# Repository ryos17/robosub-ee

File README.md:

# Stanford RoboSub — Electrical Repo

Electrical subsystem for the Stanford RoboSub AUV. It includes PCB designs (KiCad), firmware, Python tools, and research.

🌐 [stanfordrobosub.org](https://www.stanfordrobosub.org/)

## Repository layout

- **`platformio.ini`** — PlatformIO config for building/flashing the Teensy firmware. `src_dir` points at one sketch folder; change it to pick which firmware gets flashed (see comments in the file).
- **`gen1/`** — First hardware generation: PCBs only. Deprecated; the sub no longer exists.
- **`gen2/`** — Second (current) generation: PCBs and firmware for the audio and Teensy boards.
- **`gen3/`** — Third generation (in progress): ongoing designs of PCBs with Micro Breakout, Battery Boards, Power Distribution.
- **`imported_parts/`** — Shared KiCad libraries: symbols, footprints, 3D models, import script, and the JLC parts order log.
- **`misc/`** — Older and experimental material.
- **`research/`** — Research work (whisper-based intervehicle communication).

## Sub setup (Jetson Orin)

### Fix the system clock

The Jetson has no battery-backed RTC, so after being powered off its clock can be wrong. A wrong date breaks TLS, so Claude Code, `git`, `pip`, etc. fail to connect. Fix it by syncing over the internet:

```bash
timedatectl                      # check: "System clock synchronized" and the date
sudo timedatectl set-ntp true    # sync the time over the internet
sudo systemctl restart systemd-timesyncd
timedatectl                      # the date should now be correct
```

### Connect to eduroam (Stanford)

Replace `SUNETID` and the password with your own (Stanford eduroam uses PEAP / MSCHAPv2 with `sunetid@stanford.edu` as the identity):

```bash
nmcli connection add type wifi ifname wlP1p1s0 con-name eduroam ssid eduroam \
  wifi-sec.key-mgmt wpa-eap 802-1x.eap peap 802-1x.phase2-auth mschapv2 \
  802-1x.identity SUNETID@stanford.edu 802-1x.password 'YOUR_PASSWORD'
nmcli connection up eduroam
```

If an `eduroam` connection already exists, update it instead of adding a new one:

```bash
nmcli connection modify eduroam 802-1x.identity SUNETID@stanford.edu 802-1x.password 'YOUR_PASSWORD'
nmcli connection up eduroam
```

Don't commit your password. Afterwards, run the clock fix above if Claude still can't connect.

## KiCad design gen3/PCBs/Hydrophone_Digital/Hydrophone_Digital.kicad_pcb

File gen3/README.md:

# Gen 3 Submarine (in progress)

The third hardware generation, currently being designed. The proposed system
architecture is shown below; the boards under [`PCBs/`](PCBs/) are the work
toward it. The current working vehicle is still [`gen2/`](../gen2/).

## PCBs

- **`Micro_Breakout/`** — the main breakout board for gen 3, the successor to
  the gen 2 MLU breakout. References the shared parts library in
  [`../../imported_parts`](../../imported_parts).
- **`Battery_Boards/`** — the gen 3 power-management / battery boards, the
  follow-on to the gen 2 `Power_Management` boards (which had heat problems).
  Two design variants:
  - **`Power_ManagementV3_diode/`** — the diode-based design; this is the lead
    design.
  - **`Power_ManagementV3_eli/`** — Eli's alternative design, kept as a backup.
- **`Power_Distribution/`** — the gen 3 power-distribution board (battery →
  rails).
- **`to_order/`** — staging area for boards that are ready to be fabricated
  (currently empty).

## TODO

- Finalize how signals/power route in and out of `Micro_Breakout`, and choose
  the physical dimensions of all the boards.
- Order the PCBs.

_Last updated: 2026-07-20_

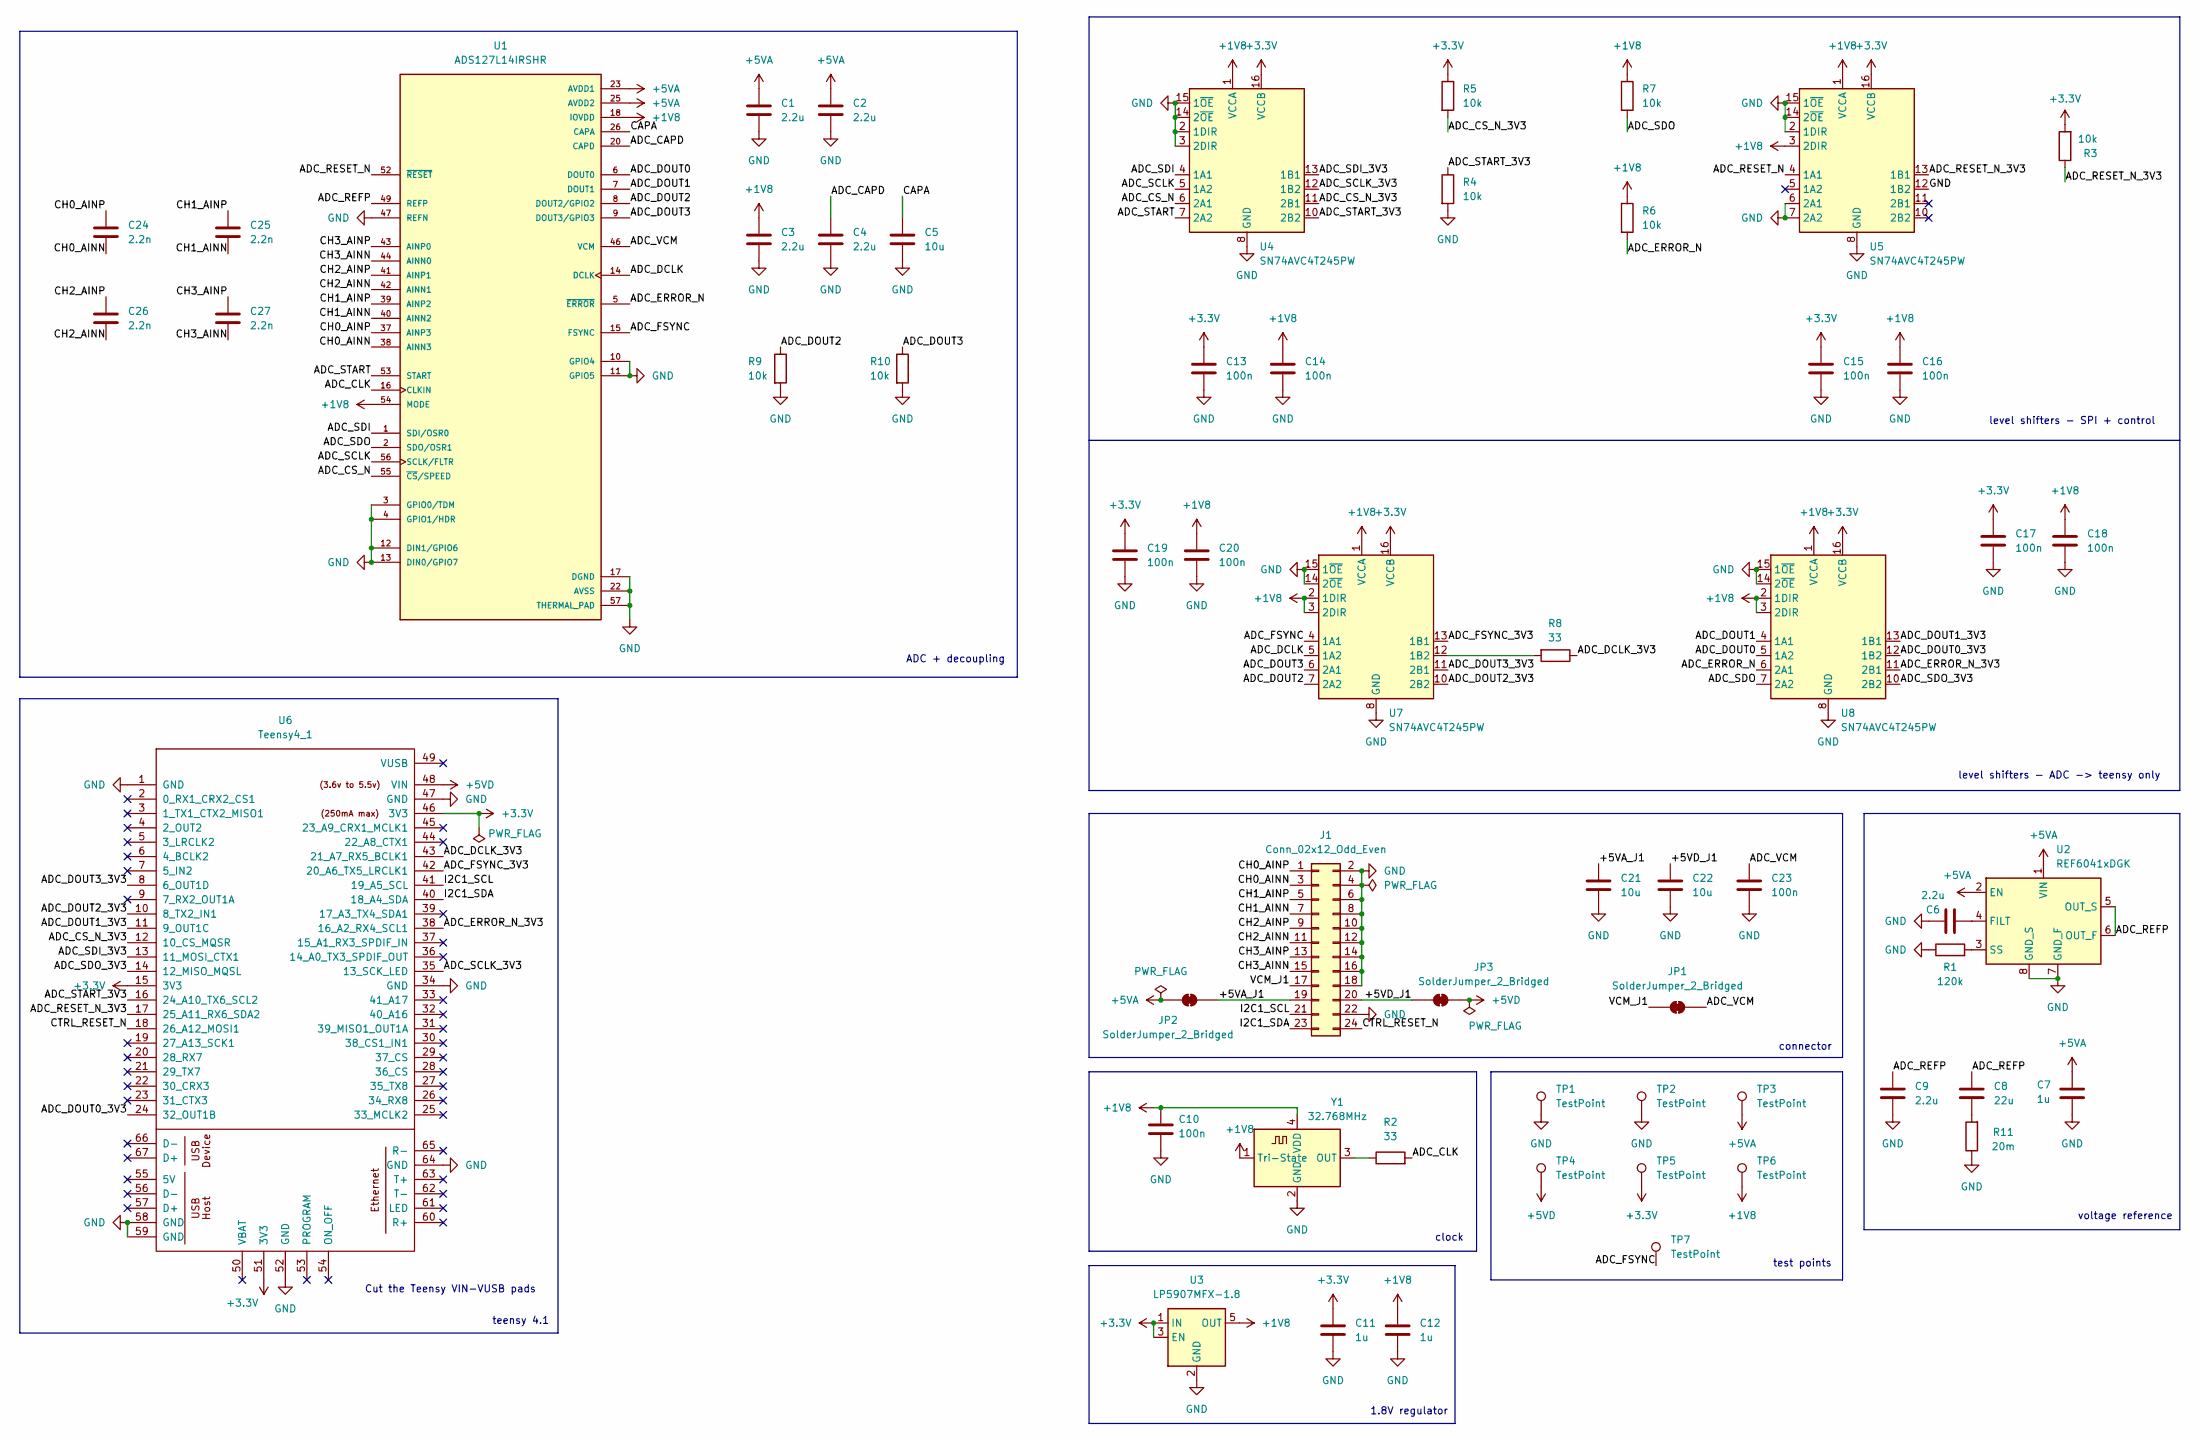
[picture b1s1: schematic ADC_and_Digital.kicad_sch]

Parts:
C1, C2, C3, C4, C6, C9: 2.2u; C_0805_2012Metric_Pad1.18x1.45mm_HandSolder; LCSC C19110
C5, C21, C22: 10u; C_1206_3216Metric_Pad1.33x1.80mm_HandSolder; LCSC C13585
C7, C11, C12: 1u; C_0805_2012Metric_Pad1.18x1.45mm_HandSolder; LCSC C28323
C8: 22u; C_1206_3216Metric_Pad1.33x1.80mm_HandSolder; LCSC C12891
C10, C13, C14, C15, C16, C17, C18, C19, C20, C23: 100n; C_0805_2012Metric_Pad1.18x1.45mm_HandSolder; LCSC C49678
C24, C25, C26, C27: 2.2n; C_0805_2012Metric_Pad1.18x1.45mm_HandSolder; LCSC C28260
J1: Conn_02x12_Odd_Even; PinSocket_2x12_P2.54mm_Horizontal; LCSC C22373936
JP1, JP2, JP3: SolderJumper_2_Bridged; SolderJumper-2_P1.3mm_Bridged_RoundedPad1.0x1.5mm
R1: 120k; R_0805_2012Metric_Pad1.20x1.40mm_HandSolder; LCSC C17436
R2, R8: 33; R_0805_2012Metric_Pad1.20x1.40mm_HandSolder; LCSC C17634
R3, R4, R5, R6, R7, R9, R10: 10k; R_0805_2012Metric_Pad1.20x1.40mm_HandSolder; LCSC C17414
R11: 20m; R_0805_2012Metric_Pad1.20x1.40mm_HandSolder; LCSC C163095
TP1, TP2, TP3, TP4: TestPoint; TestPoint_THTPad_D2.0mm_Drill1.0mm
TP5, TP6: TestPoint; TestPoint_Pad_D1.5mm
TP7: TestPoint; TestPoint_Pad_D1.0mm
U1: ADS127L14IRSHR; IC_ADS127L14IRSHR; PARTREV B; LCSC C46377303
U2: REF6041xDGK; VSSOP-8_3x3mm_P0.65mm; LCSC C2157051
U3: LP5907MFX-1.8; SOT-23-5; LCSC C92498
U4, U5, U7, U8: SN74AVC4T245PW; TSSOP-16_4.4x5mm_P0.65mm; LCSC C81461
U6: Teensy4_1
Y1: 32.768MHz; Oscillator_SMD_ECS_2520MV-xxx-xx-4Pin_2.5x2.0mm; LCSC C5452669

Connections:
+1V8: C3.2, C10.1, C12.1, C14.1, C16.1, C18.1, C20.1, R6.1, R7.1, TP6.1 (1_1), U1.18 (IOVDD), U1.19 (IOVDD), U1.54 (MODE), U3.5 (OUT), U4.1 (VCCA), U5.1 (VCCA), U5.3 (2DIR), U7.1 (VCCA), U7.2 (1DIR), U7.3 (2DIR), U8.1 (VCCA), U8.2 (1DIR), U8.3 (2DIR), Y1.1 (Tri-State), Y1.4 (VDD)
+3.3V: C11.1, C13.1, C15.1, C17.1, C19.1, R3.2, R5.1, TP5.1 (1_1), U3.1 (IN), U3.3 (EN), U4.16 (VCCB), U5.16 (VCCB), U6.15 (3V3), U6.46 (3V3), U6.51 (3V3), U7.16 (VCCB), U8.16 (VCCB)
+5VA: C1.2, C2.2, C7.1, JP2.1 (A), TP3.1 (1_1), U1.23 (AVDD1), U1.24 (AVDD1), U1.25 (AVDD2), U2.1 (VIN), U2.2 (EN)
+5VD: JP3.2 (B), TP4.1 (1_1), U6.48 (VIN)
/ADC_and_Digital/+5VA_J1: C21.1, J1.19, JP2.2 (B)
/ADC_and_Digital/+5VD_J1: C22.1, J1.20, JP3.1 (A)
/ADC_and_Digital/ADC_CAPD: C4.2, U1.20 (CAPD)
/ADC_and_Digital/ADC_CLK: R2.2, U1.16 (CLKIN)
/ADC_and_Digital/ADC_CS_N: U1.55 (~CS/SPEED), U4.6 (2A1)
/ADC_and_Digital/ADC_CS_N_3V3: R5.2, U4.11 (2B1), U6.12 (10_CS_MQSR)
/ADC_and_Digital/ADC_DCLK: U1.14 (DCLK), U7.5 (1A2)
/ADC_and_Digital/ADC_DCLK_3V3: R8.1, U6.43 (21_A7_RX5_BCLK1)
/ADC_and_Digital/ADC_DOUT0: U1.6 (DOUT0), U8.5 (1A2)
/ADC_and_Digital/ADC_DOUT0_3V3: U6.24 (32_OUT1B), U8.12 (1B2)
/ADC_and_Digital/ADC_DOUT1: U1.7 (DOUT1), U8.4 (1A1)
/ADC_and_Digital/ADC_DOUT1_3V3: U6.11 (9_OUT1C), U8.13 (1B1)
/ADC_and_Digital/ADC_DOUT2: R9.1, U1.8 (DOUT2/GPIO2), U7.7 (2A2)
/ADC_and_Digital/ADC_DOUT2_3V3: U6.10 (8_TX2_IN1), U7.10 (2B2)
/ADC_and_Digital/ADC_DOUT3: R10.1, U1.9 (DOUT3/GPIO3), U7.6 (2A1)
/ADC_and_Digital/ADC_DOUT3_3V3: U6.8 (6_OUT1D), U7.11 (2B1)
/ADC_and_Digital/ADC_ERROR_N: R6.2, U1.5 (~ERROR), U8.6 (2A1)
/ADC_and_Digital/ADC_ERROR_N_3V3: U6.38 (16_A2_RX4_SCL1), U8.11 (2B1)
/ADC_and_Digital/ADC_FSYNC: TP7.1 (1_1), U1.15 (FSYNC), U7.4 (1A1)
/ADC_and_Digital/ADC_FSYNC_3V3: U6.42 (20_A6_TX5_LRCLK1), U7.13 (1B1)
/ADC_and_Digital/ADC_REFP: C8.1, C9.1, U1.49 (REFP), U1.50 (REFP), U2.5 (OUT_S), U2.6 (OUT_F)
/ADC_and_Digital/ADC_RESET_N: U1.52 (~RESET), U5.4 (1A1)
/ADC_and_Digital/ADC_RESET_N_3V3: R3.1, U5.13 (1B1), U6.17 (25_A11_RX6_SDA2)
/ADC_and_Digital/ADC_SCLK: U1.56 (SCLK/FLTR), U4.5 (1A2)
/ADC_and_Digital/ADC_SCLK_3V3: U4.12 (1B2), U6.35 (13_SCK_LED)
/ADC_and_Digital/ADC_SDI: U1.1 (SDI/OSR0), U4.4 (1A1)
/ADC_and_Digital/ADC_SDI_3V3: U4.13 (1B1), U6.13 (11_MOSI_CTX1)
/ADC_and_Digital/ADC_SDO: R7.2, U1.2 (SDO/OSR1), U8.7 (2A2)
/ADC_and_Digital/ADC_SDO_3V3: U6.14 (12_MISO_MQSL), U8.10 (2B2)
/ADC_and_Digital/ADC_START: U1.53 (START), U4.7 (2A2)
/ADC_and_Digital/ADC_START_3V3: R4.1, U4.10 (2B2), U6.16 (24_A10_TX6_SCL2)
/ADC_and_Digital/ADC_VCM: C23.1, JP1.2 (B), U1.46 (VCM)
/ADC_and_Digital/CH0_AINN: C24.1, J1.3, U1.38 (AINN3)
/ADC_and_Digital/CH0_AINP: C24.2, J1.1, U1.37 (AINP3)
/ADC_and_Digital/CH1_AINN: C25.1, J1.7, U1.40 (AINN2)
/ADC_and_Digital/CH1_AINP: C25.2, J1.5, U1.39 (AINP2)
/ADC_and_Digital/CH2_AINN: C26.1, J1.11, U1.42 (AINN1)
/ADC_and_Digital/CH2_AINP: C26.2, J1.9, U1.41 (AINP1)
/ADC_and_Digital/CH3_AINN: C27.1, J1.15, U1.44 (AINN0)
/ADC_and_Digital/CH3_AINP: C27.2, J1.13, U1.43 (AINP0)
/ADC_and_Digital/CTRL_RESET_N: J1.24, U6.18 (26_A12_MOSI1)
/ADC_and_Digital/I2C1_SCL: J1.21, U6.41 (19_A5_SCL)
/ADC_and_Digital/I2C1_SDA: J1.23, U6.40 (18_A4_SDA)
/ADC_and_Digital/VCM_J1: J1.17, JP1.1 (A)
CAPA: C5.2, U1.26 (CAPA), U1.27 (CAPA)
GND: C1.1, C2.1, C3.1, C4.1, C5.1, C6.1, C7.2, C9.2, C10.2, C11.2, C12.2, C13.2, C14.2, C15.2, C16.2, C17.2, C18.2, C19.2, C20.2, C21.2, C22.2, C23.2, J1.2, J1.4, J1.6, J1.8, J1.10, J1.12, J1.14, J1.16, J1.18, J1.22, R1.1, R4.2, R9.2, R10.2, R11.1, TP1.1 (1_1), TP2.1 (1_1), U1.3 (GPIO0/TDM), U1.4 (GPIO1/HDR), U1.10 (GPIO4), U1.11 (GPIO5), U1.12 (DIN1/GPIO6), U1.13 (DIN0/GPIO7), U1.17 (DGND), U1.21 (DGND), U1.22 (AVSS), U1.28 (AVSS), U1.29 (AVSS), U1.30 (AVSS), U1.31 (AVSS), U1.32 (AVSS), U1.33 (AVSS), U1.34 (AVSS), U1.35 (AVSS), U1.36 (AVSS), U1.45 (AVSS), U1.47 (REFN), U1.48 (REFN), U1.51 (AVSS), U1.57 (THERMAL_PAD), U2.7 (GND_F), U2.8 (GND_S), U3.2 (GND), U4.2 (1DIR), U4.3 (2DIR), U4.8 (GND), U4.9 (GND), U4.14 (2~OE), U4.15 (1~OE), U5.2 (1DIR), U5.6 (2A1), U5.7 (2A2), U5.8 (GND), U5.9 (GND), U5.12 (1B2), U5.14 (2~OE), U5.15 (1~OE), U6.1 (GND), U6.34 (GND), U6.47 (GND), U6.52 (GND), U6.58 (GND), U6.59 (GND), U6.64 (GND), U7.8 (GND), U7.9 (GND), U7.14 (2~OE), U7.15 (1~OE), U8.8 (GND), U8.9 (GND), U8.14 (2~OE), U8.15 (1~OE), Y1.2 (GND)
unnamed: C8.2, R11.2
unnamed: C6.2, U2.4 (FILT)
unnamed: R1.2, U2.3 (SS)
unnamed: R8.2, U7.12 (1B2)
unnamed: R2.1, Y1.3 (OUT)

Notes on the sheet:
level shifters - SPI + control
Cut the Teensy VIN-VUSB pads
clock
test points
connector
voltage reference
ADC + decoupling
level shifters - ADC -> teensy only
teensy 4.1
1.8V regulator

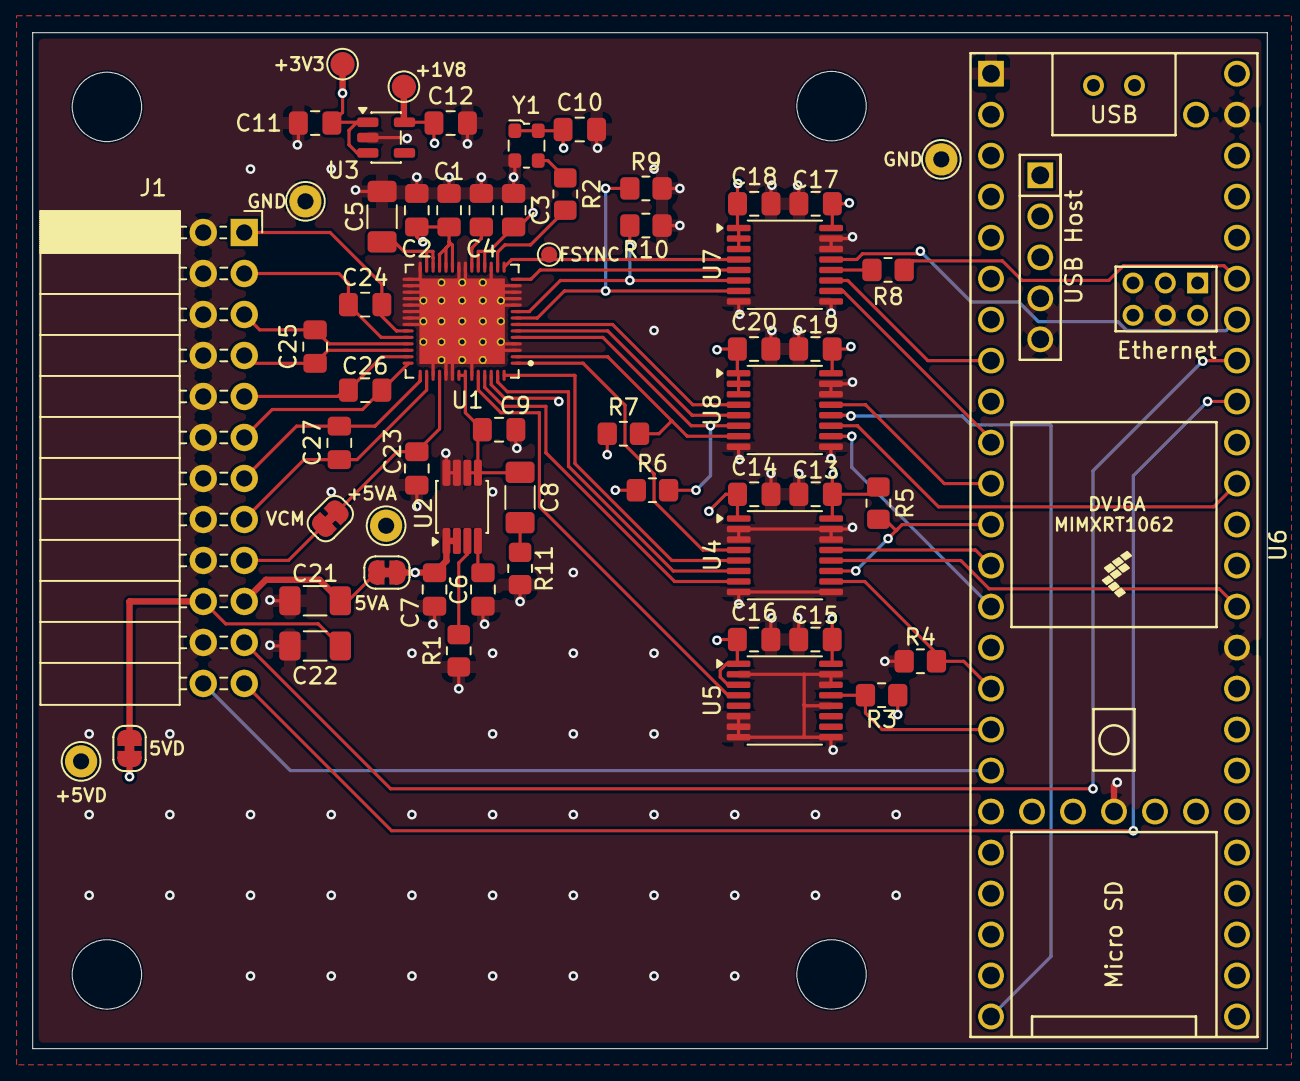
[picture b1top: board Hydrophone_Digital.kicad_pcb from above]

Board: 4 copper layers, 76.5 x 63.0 mm, 62 parts (0 on the bottom side), 55 nets.

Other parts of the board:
H1, H2, H3, H4: MountingHole_4.3mm_M4

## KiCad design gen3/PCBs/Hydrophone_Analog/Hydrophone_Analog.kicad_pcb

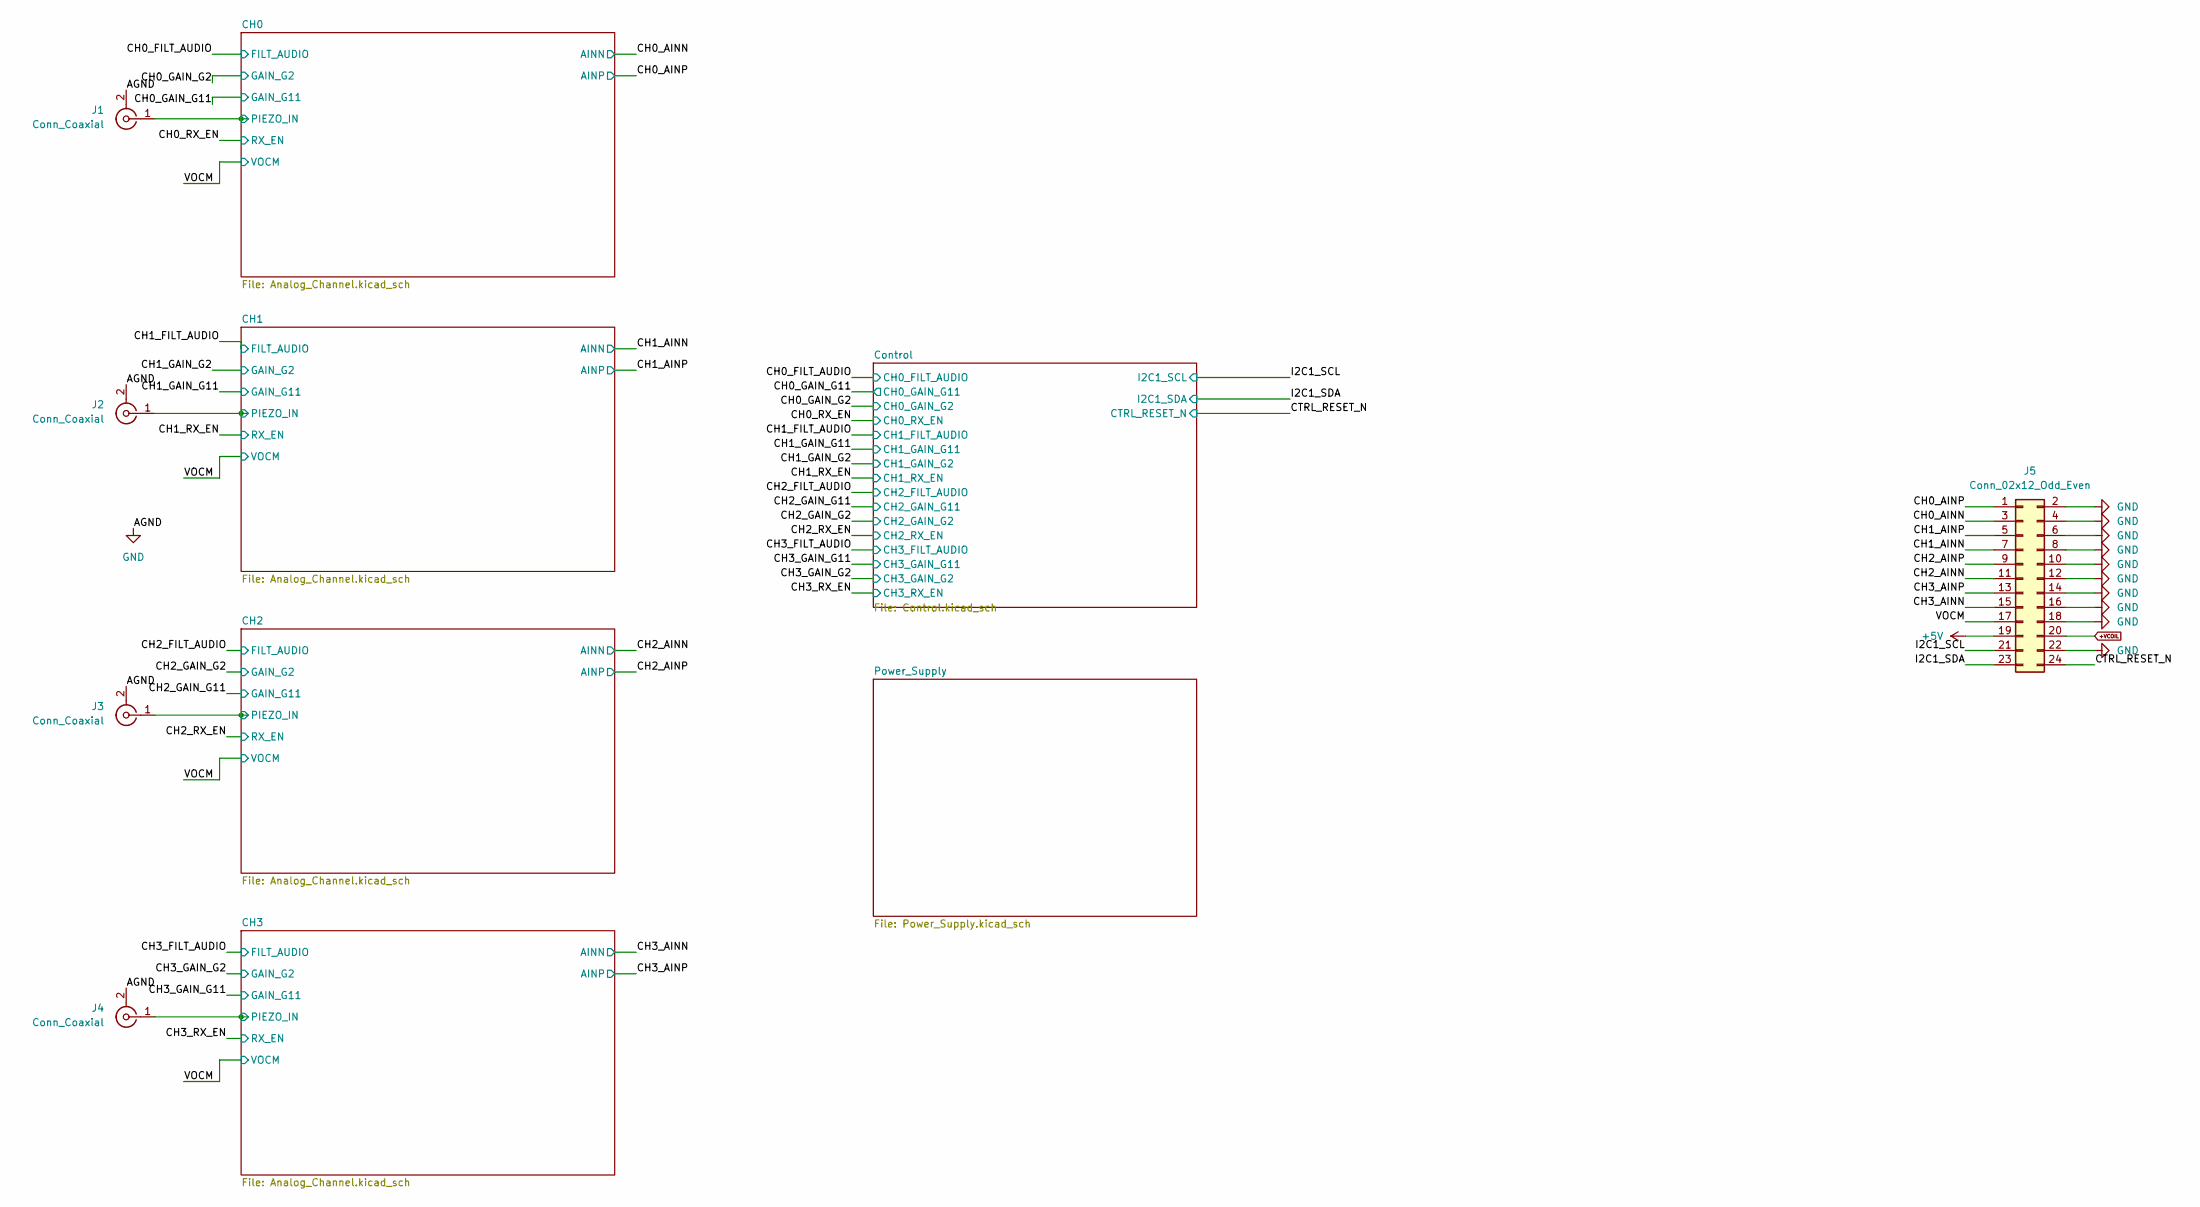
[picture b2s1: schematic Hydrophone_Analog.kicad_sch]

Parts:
J1, J2, J3, J4: Conn_Coaxial; PinHeader_1x02_P2.54mm_Vertical
J5: Conn_02x12_Odd_Even; PinHeader_2x12_P2.54mm_Vertical

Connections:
+5V: J5.19; also elsewhere on the board
+VCOIL: J5.20; also elsewhere on the board
/CH0/PIEZO_IN: J1.1 (In); also elsewhere on the board
/CH0_AINN: J5.3; also elsewhere on the board
/CH0_AINP: J5.1; also elsewhere on the board
/CH1/PIEZO_IN: J2.1 (In); also elsewhere on the board
/CH1_AINN: J5.7; also elsewhere on the board
/CH1_AINP: J5.5; also elsewhere on the board
/CH2/PIEZO_IN: J3.1 (In); also elsewhere on the board
/CH2_AINN: J5.11; also elsewhere on the board
/CH2_AINP: J5.9; also elsewhere on the board
/CH3/PIEZO_IN: J4.1 (In); also elsewhere on the board
/CH3_AINN: J5.15; also elsewhere on the board
/CH3_AINP: J5.13; also elsewhere on the board
/CTRL_RESET_N: J5.24; also elsewhere on the board
/I2C1_SCL: J5.21; also elsewhere on the board
/I2C1_SDA: J5.23; also elsewhere on the board
/VOCM: J5.17; also elsewhere on the board
GND: J1.2 (Ext), J2.2 (Ext), J3.2 (Ext), J4.2 (Ext), J5.2, J5.4, J5.6, J5.8, J5.10, J5.12, J5.14, J5.16, J5.18, J5.22; also elsewhere on the board

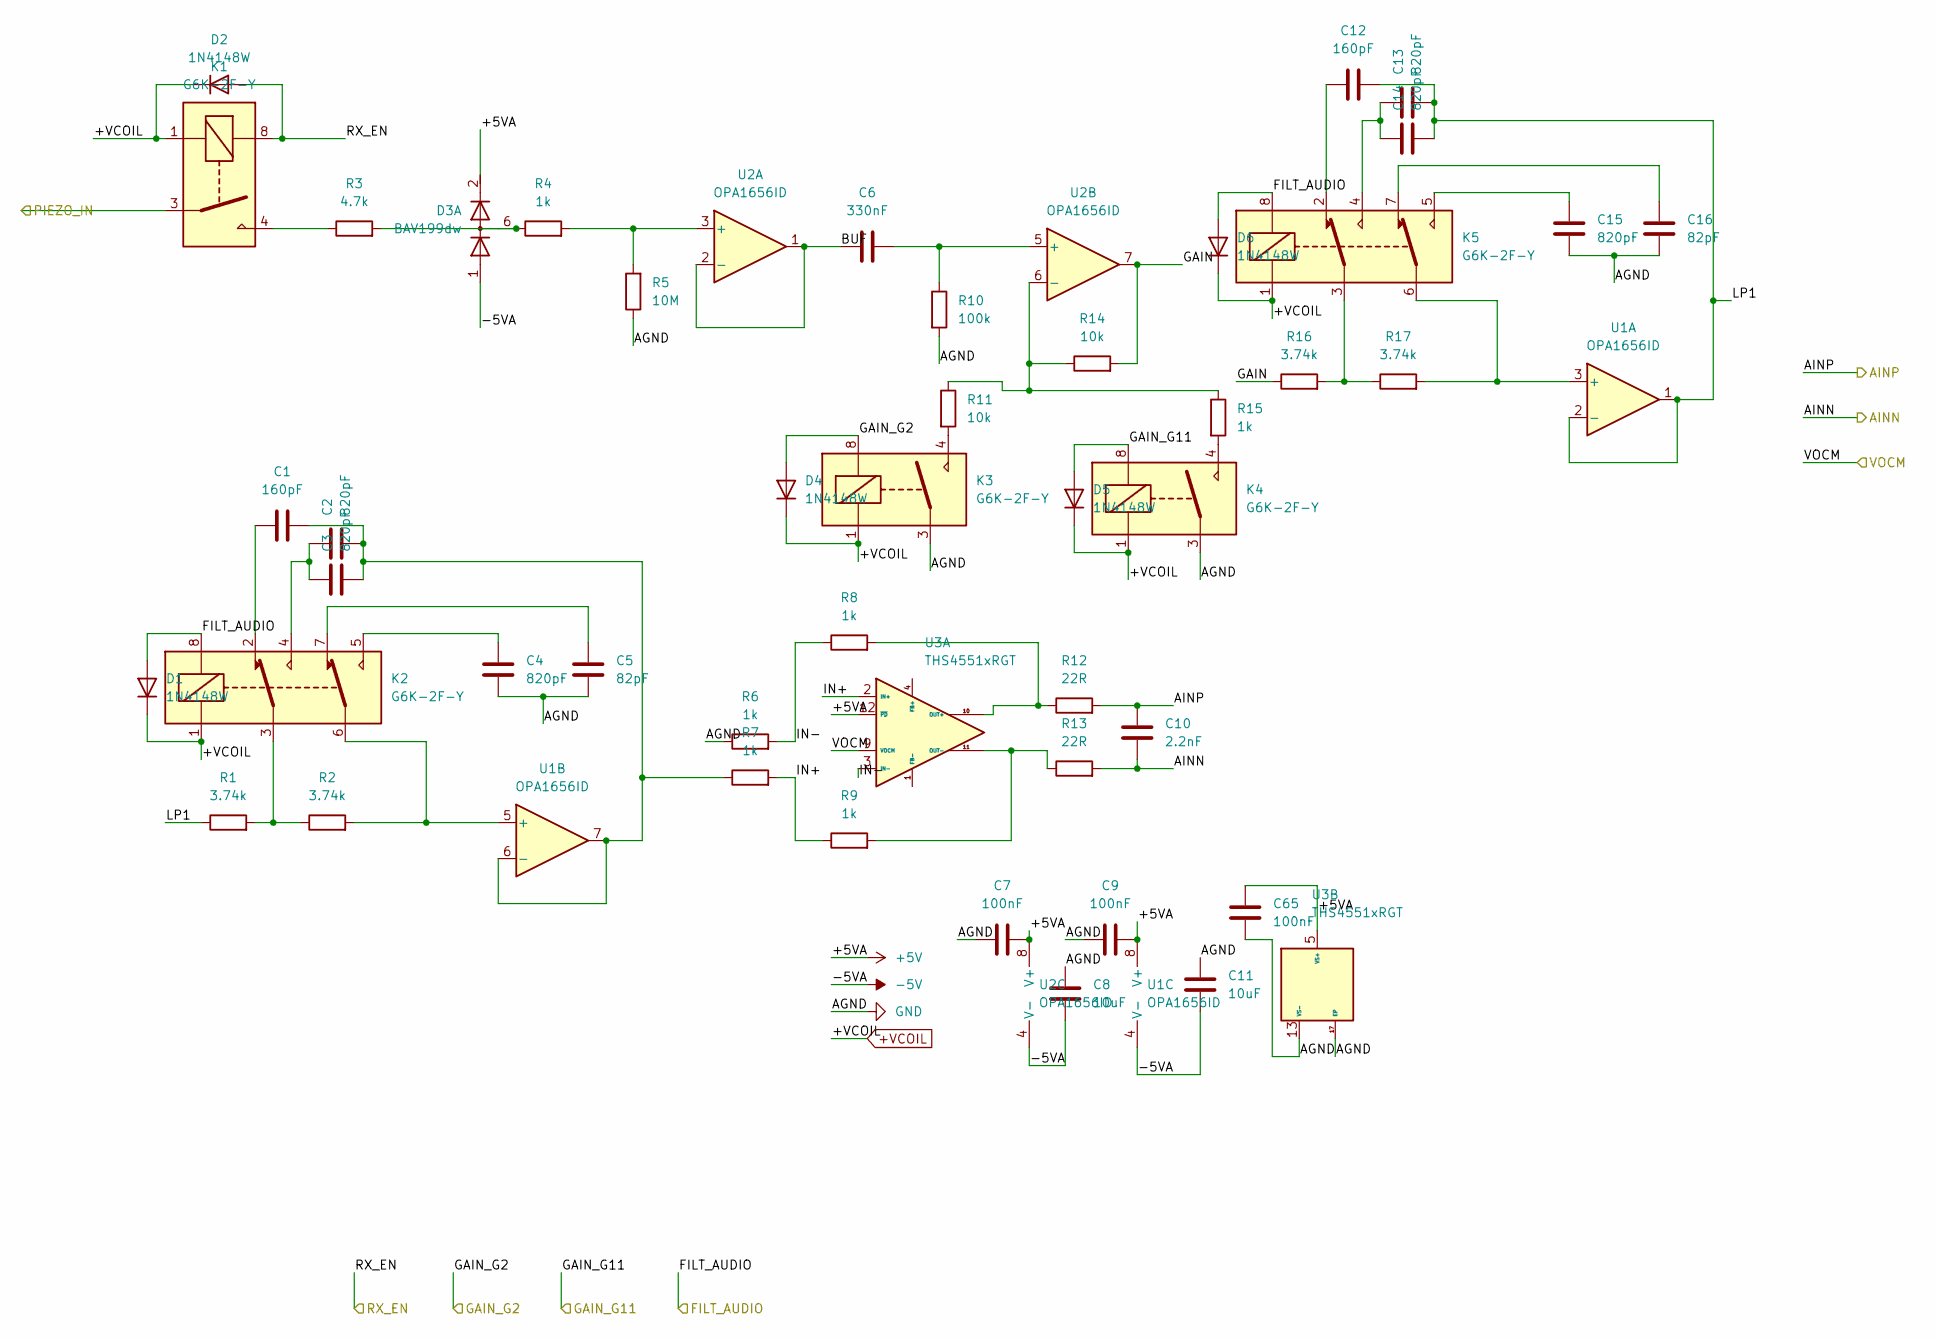
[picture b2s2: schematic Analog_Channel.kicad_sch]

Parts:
C1, C12: 160pF; C_0805_2012Metric
C2, C3, C4, C13, C14, C15: 820pF; C_0805_2012Metric
C5, C16: 82pF; C_0805_2012Metric
C6: 330nF; C_0805_2012Metric
C7, C9, C65: 100nF; C_0805_2012Metric
C8, C11: 10uF; C_1206_3216Metric
C10: 2.2nF; C_0805_2012Metric
D1, D2, D4, D5, D6: 1N4148W; D_SOD-123
D3: BAV199dw; SOT-363_SC-70-6
K1, K2, K3, K4, K5: G6K-2F-Y; Relay_DPDT_Omron_G6K-2F-Y
R1, R2, R16, R17: 3.74k; R_0805_2012Metric
R3: 4.7k; R_0805_2012Metric
R4, R6, R7, R8, R9, R15: 1k; R_0805_2012Metric
R5: 10M; R_0805_2012Metric
R10: 100k; R_0805_2012Metric
R11, R14: 10k; R_0805_2012Metric
R12, R13: 22R; R_0805_2012Metric
U1, U2: OPA1656ID; SOIC-8_3.9x4.9mm_P1.27mm
U3: THS4551xRGT; VQFN-16-1EP_3x3mm_P0.5mm_EP1.68x1.68mm

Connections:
+5V: C7.2, C9.2, C65.2, D3.2 (K2), U1.8 (V+), U2.8 (V+), U3.5 (VS+), U3.6 (VS+), U3.7 (VS+), U3.8 (VS+), U3.12 (~PD); also elsewhere on the board
+VCOIL: D1.1 (K), D2.1 (K), D4.1 (K), D5.1 (K), D6.1 (K), K1.1 (A2), K2.1 (A2), K3.1 (A2), K4.1 (A2), K5.1 (A2); also elsewhere on the board
-5V: C8.2, C11.2, D3.1 (A1), U1.4 (V-), U2.4 (V-); also elsewhere on the board
/CH0/BUF: C6.1, U2.1, U2.2 (-)
/CH0/GAIN: R14.2, R16.1, U2.7
/CH0/IN+: R7.2, R9.1, U3.2 (IN+)
/CH0/IN-: R6.2, R8.1, U3.3 (IN-)
/CH0/LP1: C12.2, C13.2, C14.2, R1.1, U1.1, U1.2 (-)
/CH0/PIEZO_IN: K1.3 (13); also elsewhere on the board
/CH0_AINN: C10.2, R13.2; also elsewhere on the board
/CH0_AINP: C10.1, R12.2; also elsewhere on the board
/CH0_FILT_AUDIO: D1.2 (A), D6.2 (A), K2.8 (A1), K5.8 (A1); also elsewhere on the board
/CH0_GAIN_G2: D4.2 (A), K3.8 (A1); also elsewhere on the board
/CH0_GAIN_G11: D5.2 (A), K4.8 (A1); also elsewhere on the board
/CH0_RX_EN: D2.2 (A), K1.8 (A1); also elsewhere on the board
/VOCM: U3.9 (VOCM); also elsewhere on the board
GND: C4.2, C5.2, C7.1, C8.1, C9.1, C11.1, C15.2, C16.2, C65.1, K3.3 (13), K4.3 (13), R5.1, R6.1, R10.2, U3.13 (VS-), U3.14 (VS-), U3.15 (VS-), U3.16 (VS-), U3.17 (EP); also elsewhere on the board
unnamed: D3.6 (K3A4), R3.2, R4.1
unnamed: K1.4 (14), R3.1
unnamed: K2.3 (11), R1.2, R2.1
unnamed: C1.1, K2.2 (12)
unnamed: C2.1, C3.1, K2.4 (14)
unnamed: K2.6 (21), R2.2, U1.5 (+)
unnamed: C5.1, K2.7 (22)
unnamed: C4.1, K2.5 (24)
unnamed: K3.4 (14), R11.2
unnamed: K4.4 (14), R15.2
unnamed: K5.3 (11), R16.2, R17.1
unnamed: C12.1, K5.2 (12)
unnamed: C13.1, C14.1, K5.4 (14)
unnamed: K5.6 (21), R17.2, U1.3 (+)
unnamed: C16.1, K5.7 (22)
unnamed: C15.1, K5.5 (24)
unnamed: C1.2, C2.2, C3.2, R7.1, U1.6 (-), U1.7
unnamed: R4.2, R5.2, U2.3 (+)
unnamed: C6.2, R10.1, U2.5 (+)
unnamed: R11.1, R14.1, R15.1, U2.6 (-)
unnamed: R8.2, R12.1, U3.10 (OUT+)
unnamed: R9.2, R13.1, U3.11 (OUT-)

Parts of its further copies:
C17, C28, C33, C44, C49, C60: 160pF; C_0805_2012Metric
C18, C19, C20, C29, C30, C31, C34, C35, C36, C45, C46, C47, C50, C51, C52, C61, C62, C63: 820pF; C_0805_2012Metric
C21, C32, C37, C48, C53, C64: 82pF; C_0805_2012Metric
C22, C38, C54: 330nF; C_0805_2012Metric
C23, C25, C39, C41, C55, C57, C66, C67, C68: 100nF; C_0805_2012Metric
C24, C27, C40, C43, C56, C59: 10uF; C_1206_3216Metric
C26, C42, C58: 2.2nF; C_0805_2012Metric
D7, D8, D10, D11, D12, D13, D14, D16, D17, D18, D19, D20, D22, D23, D24: 1N4148W; D_SOD-123
D9, D15, D21: BAV199dw; SOT-363_SC-70-6
K6, K7, K8, K9, K10, K11, K12, K13, K14, K15, K16, K17, K18, K19, K20: G6K-2F-Y; Relay_DPDT_Omron_G6K-2F-Y
R18, R19, R33, R34, R35, R36, R50, R51, R52, R53, R67, R68: 3.74k; R_0805_2012Metric
R20, R37, R54: 4.7k; R_0805_2012Metric
R21, R23, R24, R25, R26, R32, R38, R40, R41, R42, R43, R49, R55, R57, R58, R59, R60, R66: 1k; R_0805_2012Metric
R22, R39, R56: 10M; R_0805_2012Metric
R27, R44, R61: 100k; R_0805_2012Metric
R28, R31, R45, R48, R62, R65: 10k; R_0805_2012Metric
R29, R30, R46, R47, R63, R64: 22R; R_0805_2012Metric
U4, U5, U10, U11, U16, U17: OPA1656ID; SOIC-8_3.9x4.9mm_P1.27mm
U6, U12, U18: THS4551xRGT; VQFN-16-1EP_3x3mm_P0.5mm_EP1.68x1.68mm

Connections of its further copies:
+5V: C23.2, C25.2, C39.2, C41.2, C55.2, C57.2, C66.2, C67.2, C68.2, D9.2 (K2), D15.2 (K2), D21.2 (K2), U4.8 (V+), U5.8 (V+), U6.5 (VS+), U6.6 (VS+), U6.7 (VS+), U6.8 (VS+), U6.12 (~PD), U10.8 (V+), U11.8 (V+), U12.5 (VS+), U12.6 (VS+), U12.7 (VS+), U12.8 (VS+), U12.12 (~PD), U16.8 (V+), U17.8 (V+), U18.5 (VS+), U18.6 (VS+), U18.7 (VS+), U18.8 (VS+), U18.12 (~PD); also elsewhere on the board
+VCOIL: D7.1 (K), D8.1 (K), D10.1 (K), D11.1 (K), D12.1 (K), D13.1 (K), D14.1 (K), D16.1 (K), D17.1 (K), D18.1 (K), D19.1 (K), D20.1 (K), D22.1 (K), D23.1 (K), D24.1 (K), K6.1 (A2), K7.1 (A2), K8.1 (A2), K9.1 (A2), K10.1 (A2), K11.1 (A2), K12.1 (A2), K13.1 (A2), K14.1 (A2), K15.1 (A2), K16.1 (A2), K17.1 (A2), K18.1 (A2), K19.1 (A2), K20.1 (A2); also elsewhere on the board
-5V: C24.2, C27.2, C40.2, C43.2, C56.2, C59.2, D9.1 (A1), D15.1 (A1), D21.1 (A1), U4.4 (V-), U5.4 (V-), U10.4 (V-), U11.4 (V-), U16.4 (V-), U17.4 (V-); also elsewhere on the board
/CH1/BUF: C22.1, U5.1, U5.2 (-)
/CH1/GAIN: R31.2, R33.1, U5.7
/CH1/IN+: R24.2, R26.1, U6.2 (IN+)
/CH1/IN-: R23.2, R25.1, U6.3 (IN-)
/CH1/LP1: C28.2, C29.2, C30.2, R18.1, U4.1, U4.2 (-)
/CH1/PIEZO_IN: K6.3 (13); also elsewhere on the board
/CH1_AINN: C26.2, R30.2; also elsewhere on the board
/CH1_AINP: C26.1, R29.2; also elsewhere on the board
/CH1_FILT_AUDIO: D7.2 (A), D12.2 (A), K7.8 (A1), K10.8 (A1); also elsewhere on the board
/CH1_GAIN_G2: D10.2 (A), K8.8 (A1); also elsewhere on the board
/CH1_GAIN_G11: D11.2 (A), K9.8 (A1); also elsewhere on the board
/CH1_RX_EN: D8.2 (A), K6.8 (A1); also elsewhere on the board
/CH2/BUF: C38.1, U10.1, U10.2 (-)
/CH2/GAIN: R48.2, R50.1, U10.7
/CH2/IN+: R41.2, R43.1, U12.2 (IN+)
/CH2/IN-: R40.2, R42.1, U12.3 (IN-)
/CH2/LP1: C44.2, C45.2, C46.2, R35.1, U11.1, U11.2 (-)
/CH2/PIEZO_IN: K11.3 (13); also elsewhere on the board
/CH2_AINN: C42.2, R47.2; also elsewhere on the board
/CH2_AINP: C42.1, R46.2; also elsewhere on the board
/CH2_FILT_AUDIO: D13.2 (A), D18.2 (A), K12.8 (A1), K15.8 (A1); also elsewhere on the board
/CH2_GAIN_G2: D16.2 (A), K13.8 (A1); also elsewhere on the board
/CH2_GAIN_G11: D17.2 (A), K14.8 (A1); also elsewhere on the board
/CH2_RX_EN: D14.2 (A), K11.8 (A1); also elsewhere on the board
/CH3/BUF: C54.1, U16.1, U16.2 (-)
/CH3/GAIN: R65.2, R67.1, U16.7
/CH3/IN+: R58.2, R60.1, U18.2 (IN+)
/CH3/IN-: R57.2, R59.1, U18.3 (IN-)
/CH3/LP1: C60.2, C61.2, C62.2, R52.1, U17.1, U17.2 (-)
/CH3/PIEZO_IN: K16.3 (13); also elsewhere on the board
/CH3_AINN: C58.2, R64.2; also elsewhere on the board
/CH3_AINP: C58.1, R63.2; also elsewhere on the board
/CH3_FILT_AUDIO: D19.2 (A), D24.2 (A), K17.8 (A1), K20.8 (A1); also elsewhere on the board
/CH3_GAIN_G2: D22.2 (A), K18.8 (A1); also elsewhere on the board
/CH3_GAIN_G11: D23.2 (A), K19.8 (A1); also elsewhere on the board
/CH3_RX_EN: D20.2 (A), K16.8 (A1); also elsewhere on the board
/VOCM: U6.9 (VOCM), U12.9 (VOCM), U18.9 (VOCM); also elsewhere on the board
GND: C20.2, C21.2, C23.1, C24.1, C25.1, C27.1, C31.2, C32.2, C36.2, C37.2, C39.1, C40.1, C41.1, C43.1, C47.2, C48.2, C52.2, C53.2, C55.1, C56.1, C57.1, C59.1, C63.2, C64.2, C66.1, C67.1, C68.1, K8.3 (13), K9.3 (13), K13.3 (13), K14.3 (13), K18.3 (13), K19.3 (13), R22.1, R23.1, R27.2, R39.1, R40.1, R44.2, R56.1, R57.1, R61.2, U6.13 (VS-), U6.14 (VS-), U6.15 (VS-), U6.16 (VS-), U6.17 (EP), U12.13 (VS-), U12.14 (VS-), U12.15 (VS-), U12.16 (VS-), U12.17 (EP), U18.13 (VS-), U18.14 (VS-), U18.15 (VS-), U18.16 (VS-), U18.17 (EP); also elsewhere on the board
unnamed: D9.6 (K3A4), R20.2, R21.1
unnamed: D15.6 (K3A4), R37.2, R38.1
unnamed: D21.6 (K3A4), R54.2, R55.1
unnamed: K6.4 (14), R20.1
unnamed: K7.3 (11), R18.2, R19.1
unnamed: C17.1, K7.2 (12)
unnamed: C18.1, C19.1, K7.4 (14)
unnamed: K7.6 (21), R19.2, U4.5 (+)
unnamed: C21.1, K7.7 (22)
unnamed: C20.1, K7.5 (24)
unnamed: K8.4 (14), R28.2
unnamed: K9.4 (14), R32.2
unnamed: K10.3 (11), R33.2, R34.1
unnamed: C28.1, K10.2 (12)
unnamed: C29.1, C30.1, K10.4 (14)
unnamed: K10.6 (21), R34.2, U4.3 (+)
unnamed: C32.1, K10.7 (22)
unnamed: C31.1, K10.5 (24)
unnamed: K11.4 (14), R37.1
unnamed: K12.3 (11), R35.2, R36.1
unnamed: C33.1, K12.2 (12)
unnamed: C34.1, C35.1, K12.4 (14)
unnamed: K12.6 (21), R36.2, U11.5 (+)
unnamed: C37.1, K12.7 (22)
unnamed: C36.1, K12.5 (24)
unnamed: K13.4 (14), R45.2
unnamed: K14.4 (14), R49.2
unnamed: K15.3 (11), R50.2, R51.1
unnamed: C44.1, K15.2 (12)
unnamed: C45.1, C46.1, K15.4 (14)
unnamed: K15.6 (21), R51.2, U11.3 (+)
unnamed: C48.1, K15.7 (22)
unnamed: C47.1, K15.5 (24)
unnamed: K16.4 (14), R54.1
unnamed: K17.3 (11), R52.2, R53.1
unnamed: C49.1, K17.2 (12)
unnamed: C50.1, C51.1, K17.4 (14)
unnamed: K17.6 (21), R53.2, U17.5 (+)
unnamed: C53.1, K17.7 (22)
unnamed: C52.1, K17.5 (24)
unnamed: K18.4 (14), R62.2
unnamed: K19.4 (14), R66.2
unnamed: K20.3 (11), R67.2, R68.1
unnamed: C60.1, K20.2 (12)
unnamed: C61.1, C62.1, K20.4 (14)
unnamed: K20.6 (21), R68.2, U17.3 (+)
unnamed: C64.1, K20.7 (22)
unnamed: C63.1, K20.5 (24)
unnamed: C17.2, C18.2, C19.2, R24.1, U4.6 (-), U4.7
unnamed: R21.2, R22.2, U5.3 (+)
unnamed: C22.2, R27.1, U5.5 (+)
unnamed: R28.1, R31.1, R32.1, U5.6 (-)
unnamed: R25.2, R29.1, U6.10 (OUT+)
unnamed: R26.2, R30.1, U6.11 (OUT-)
unnamed: R38.2, R39.2, U10.3 (+)
unnamed: C38.2, R44.1, U10.5 (+)
unnamed: R45.1, R48.1, R49.1, U10.6 (-)
unnamed: C33.2, C34.2, C35.2, R41.1, U11.6 (-), U11.7
unnamed: R42.2, R46.1, U12.10 (OUT+)
unnamed: R43.2, R47.1, U12.11 (OUT-)
unnamed: R55.2, R56.2, U16.3 (+)
unnamed: C54.2, R61.1, U16.5 (+)
unnamed: R62.1, R65.1, R66.1, U16.6 (-)
unnamed: C49.2, C50.2, C51.2, R58.1, U17.6 (-), U17.7
unnamed: R59.2, R63.1, U18.10 (OUT+)
unnamed: R60.2, R64.1, U18.11 (OUT-)

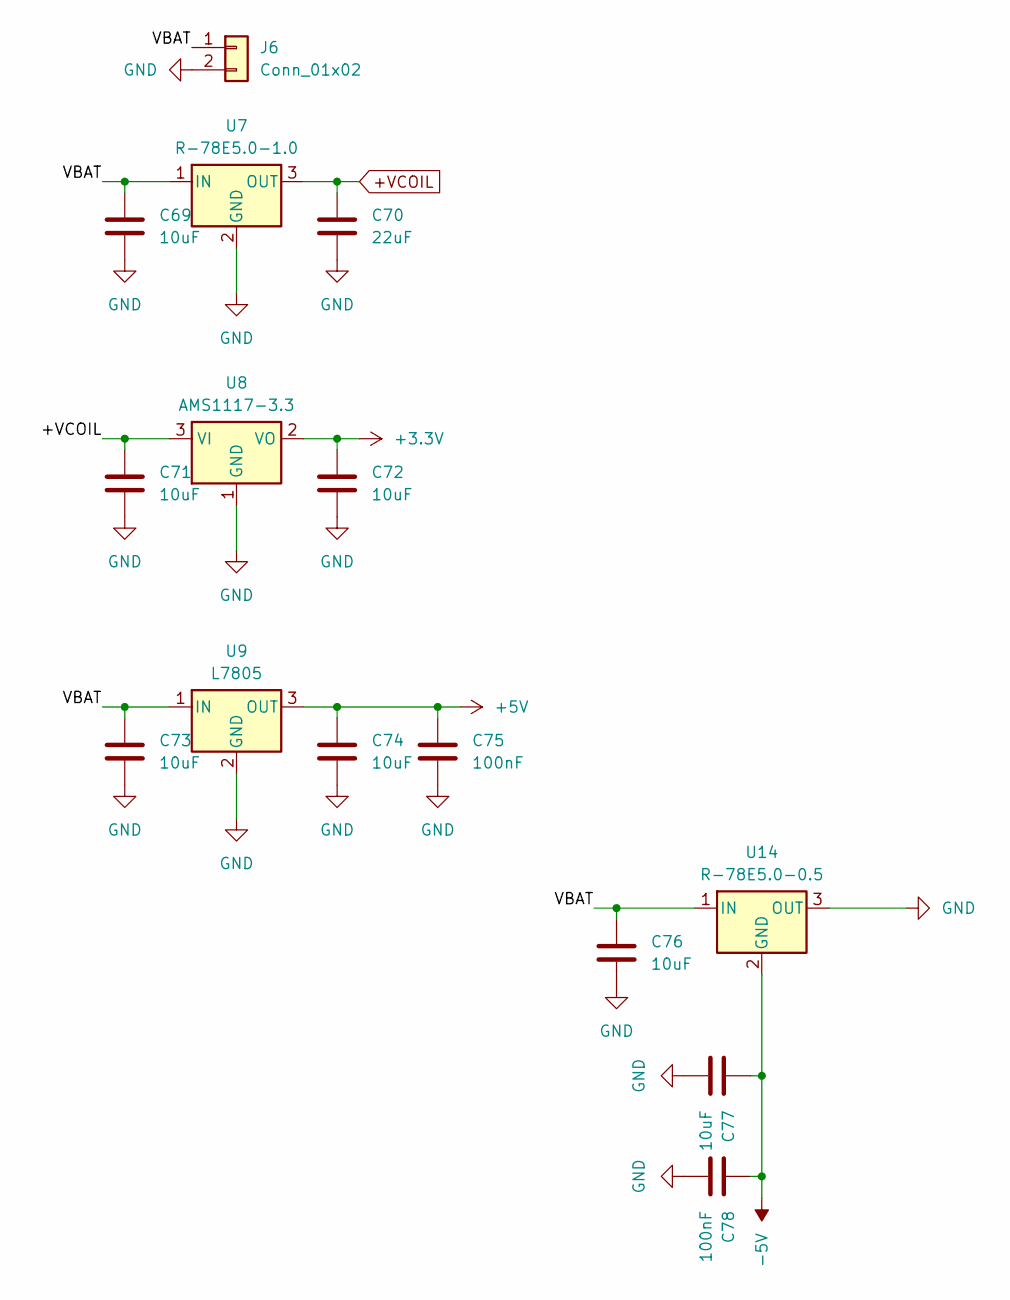
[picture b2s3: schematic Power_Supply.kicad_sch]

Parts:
C69, C71, C72, C73, C74, C76, C77: 10uF; C_1206_3216Metric
C70: 22uF; C_1206_3216Metric
C75, C78: 100nF; C_0805_2012Metric
J6: Conn_01x02; TerminalBlock_Phoenix_MKDS-1,5-2-5.08_1x02_P5.08mm_Horizont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
U7: R-78E5.0-1.0; Converter_DCDC_RECOM_R-78E-0.5_THT
U8: AMS1117-3.3; SOT-223-3_TabPin2
U9: L7805; TO-252-2
U14: R-78E5.0-0.5; Converter_DCDC_RECOM_R-78E-0.5_THT

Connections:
+3.3V: C72.1, U8.2 (VO); also elsewhere on the board
+5V: C74.1, C75.1, U9.3 (OUT); also elsewhere on the board
+VCOIL: C70.1, C71.1, U7.3 (OUT), U8.3 (VI); also elsewhere on the board
-5V: C77.1, C78.1, U14.2 (GND); also elsewhere on the board
/Power_Supply/VBAT: C69.1, C73.1, C76.1, J6.1, U7.1 (IN), U9.1 (IN), U14.1 (IN)
GND: C69.2, C70.2, C71.2, C72.2, C73.2, C74.2, C75.2, C76.2, C77.2, C78.2, J6.2, U7.2 (GND), U8.1 (GND), U9.2 (GND), U14.3 (OUT); also elsewhere on the board
